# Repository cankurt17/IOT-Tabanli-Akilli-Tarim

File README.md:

# IOT-Tabanli-Akilli-Tarim

- Bu proje tarımda sulama ve gübrelemedeki insan yüklerini azaltmak için geliştirilmiştir. Otomatik gübreleme ve 2 farklı sulama modu seçeneği ile maksimum verimde gübreleme ve sulama yapabilmektedir. Kullanıcı dostu arayüzü ve hatasız çalışma sistemi ile çiftçilerin şüphesiz tercih edeceği bir proje olması hedeflenmektedir. 
- Sistemin çalışma mantığı kullanıcı panodan veya mobil uygulamadan sulama yapacağı saat aralığını sisteme girer. Örneğin pazartesi saat 20.00 - 21.30 aralığında sisteme sulama girilmiş ise sistem belirtilen saat aralığında bahçenin suyunu açar ve kullanıcıya bilgilendirme maili gönderir. Eğer kullanıcı gübre miktarını girerek gübreleme yapılacağını sisteme belirtmiş ise sistem suyun debisini hesaplayarak girilen  miktardaki gübreyi suya aktarır ve gübrelemeyi tamamlar.
  Bütün bu sistemin çalışması sırasında bir arıza olursa kullanıcı mail ile bilgilendirilir. Örneğin su kesintisi,gübrenin bitmesi, elektrik kesintisi vb. Sulama sırasında sorun yaşanmaz ise kullanıcı bilgilendirilerek sulama kaydı tutulur ve tabloya aktarılır.
- Otomatik modda kullanıcının girdiği nem değerleri baz alınarak sistem   saatten bağımsız olarak toprağı istenilen nem aralığında tutar.Manuel modda ise kullanıcının girdiği saat aralıklarında sulama yapmaktadır. 

# Proje Özellikleri

- Otomatik ve manuel olmak üzere 2 farklı modda sulama seçeneği
- Mobil uygulama destekli
- Kullanıcı dostu kontrol panosu
- Otomatik sulama 
- Otomatik gübreleme 
- Bahçe toprağının anlık nem takibi
- Havanın sıcaklık ve nem takibi
- Gübrenin miktarı takibi
- Suyun durum ve debi takibi
- Bildirim ve mail ile bilgilendirme servisi
- Su sayacı 
- Ayrıntılı sulama kayıt tablosu
- Arıza rapor servisi 

# Prototip Görselleri

# Mobil uygulama görselleri

# Pano görselleri

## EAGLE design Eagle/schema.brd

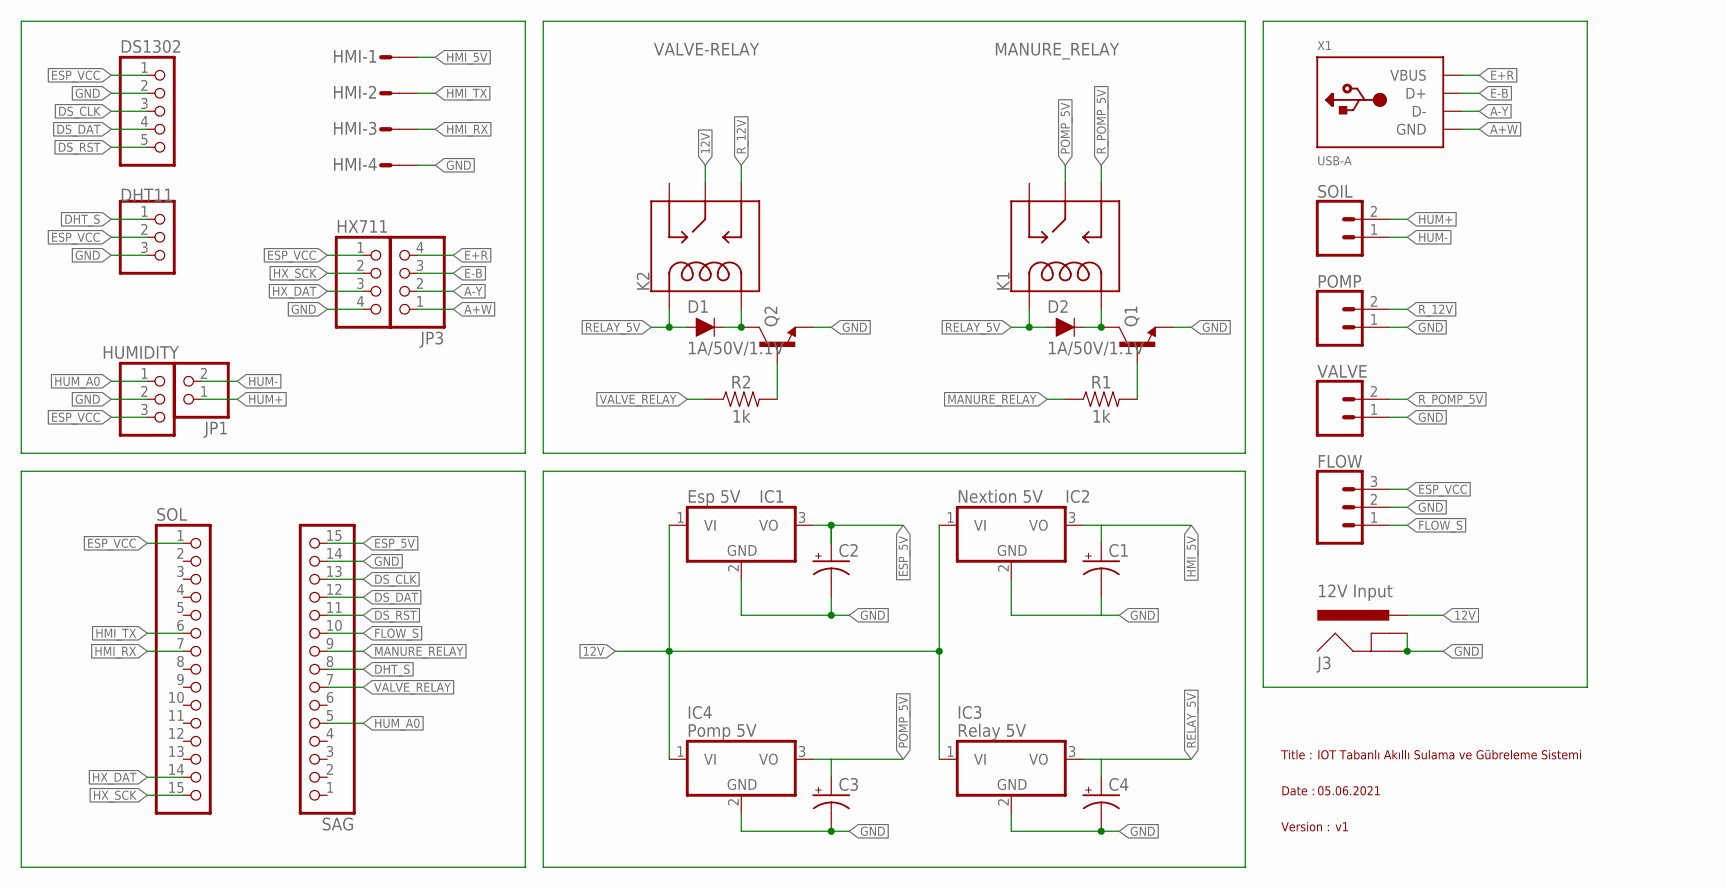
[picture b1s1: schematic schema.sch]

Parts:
C1, C2, C3, C4: CPOL-USE5-5; E5-5
D1, D2: 1A/50V/1.1V; DIODE-1N4001
DHT11: DHT11; 1X03
DS1302: PINHD-1X5; 1X05
FLOW: CONN_03JST-PTH; JST-3-PTH
HMI: L04P
HUMIDITY: PINHD-1X3; 1X03
HX711: PINHD-1X4; 1X04
IC1: Esp 5V; TO220H
IC2: Nextion 5V; TO220H
IC3: Relay 5V; TO220H
IC4: Pomp 5V; TO220H
J3: 12V Input; POWER_JACK_PTH_LOCK
JP1: PINHD-1X2; 1X02
JP3: PINHD-1X4; 1X04
K1: MANURE_RELAY; RELAY_G5LE
K2: VALVE-RELAY; RELAY_G5LE
POMP: CONN_02-JST-2-PTH-NO_SILK; JST-2-PTH-NS
Q1, Q2: 200mA/40V; TO-92
R1, R2: 1k; AXIAL-0.3
SAG: PINHD-1X15-CB; 1X15-CB
SOIL: CONN_02-JST-2-PTH-NO_SILK; JST-2-PTH-NS
SOL: PINHD-1X15-CB; 1X15-CB
VALVE: CONN_02-JST-2-PTH-NO_SILK; JST-2-PTH-NS
X1: USB-A; MOLEX_480371000

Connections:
12V: IC1.1 (VI), IC2.1 (VI), IC3.1 (VI), IC4.1 (VI), J3.PWR, K2.1 (MAIN)
A+W: JP3.1, X1.4 (GND)
A-Y: JP3.2, X1.2 (D-)
DHT_S: DHT11.1, SAG.8
DS_CLK: DS1302.3, SAG.13
DS_DAT: DS1302.4, SAG.12
DS_RST: DS1302.5, SAG.11
E+R: JP3.4, X1.1 (VBUS)
E-B: JP3.3, X1.3 (D+)
ESP_5V: C2.+, IC1.3 (VO), SAG.15
ESP_5V1: C1.+
ESP_5V2: C4.+
ESP_5V3: C3.+
ESP_VCC: DHT11.2, DS1302.1, FLOW.3, HUMIDITY.3, HX711.1, SOL.1
FLOW_S: FLOW.1, SAG.10
GND: C2.-, C3.-, C4.-, DHT11.3, DS1302.2, FLOW.2, HMI.4, HUMIDITY.2, HX711.4, IC1.2 (GND), IC2.2 (GND), IC3.2 (GND), IC4.2 (GND), J3.GND, J3.GNDBREAK, POMP.1, Q1.1 (E), Q2.1 (E), SAG.14, VALVE.1
GND2: C1.-
HMI_5V: HMI.1, IC2.3 (VO)
HMI_RX: HMI.3, SOL.7
HMI_TX: HMI.2, SOL.6
HUM+: JP1.1, SOIL.2
HUM-: JP1.2, SOIL.1
HUM_A0: HUMIDITY.1, SAG.5
HX_DAT: HX711.3, SOL.14
HX_SCK: HX711.2, SOL.15
MANURE_RELAY: R1.P$1 (1), SAG.9
unnamed: D2.C, K1.5 (COIL2), Q1.3 (C)
unnamed: Q1.2 (B), R1.P$2 (2)
unnamed: D1.C, K2.5 (COIL2), Q2.3 (C)
unnamed: Q2.2 (B), R2.P$2 (2)
POMP_5V: IC4.3 (VO), K1.1 (MAIN)
RELAY_5V: D1.A, D2.A, IC3.3 (VO), K1.2 (COIL1), K2.2 (COIL1)
R_12V: K2.3 (NO), POMP.2
R_POMP_5V: K1.3 (NO), VALVE.2
VALVE_RELAY: R2.P$1 (1), SAG.7

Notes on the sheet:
Title :
IOT Tabanlı Akıllı Sulama ve Gübreleme Sistemi
Date :
05.06.2021
Version :

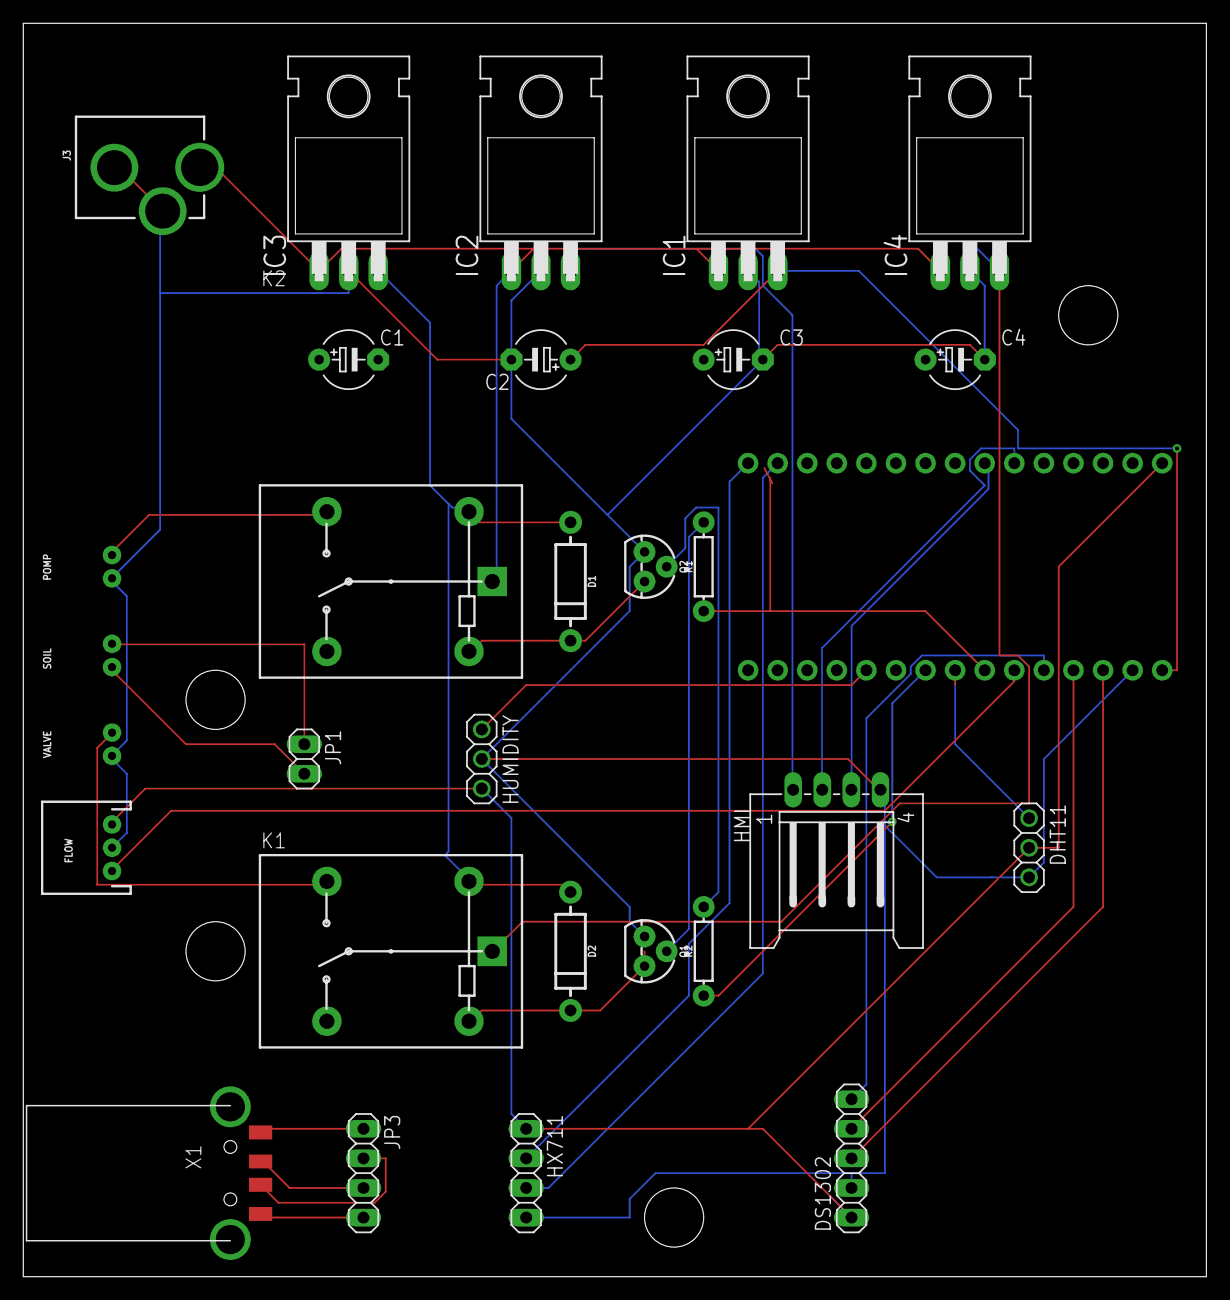
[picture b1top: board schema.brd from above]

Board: 2 copper layers, 101.6 x 107.6 mm, 31 parts (0 on the bottom side), 31 nets.

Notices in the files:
parts and their libraries:
SparkFun-Connectors: Licensing: Creative Commons ShareAlike 4.0 International - https://creativecommons.org/licenses/by-sa/4.0
